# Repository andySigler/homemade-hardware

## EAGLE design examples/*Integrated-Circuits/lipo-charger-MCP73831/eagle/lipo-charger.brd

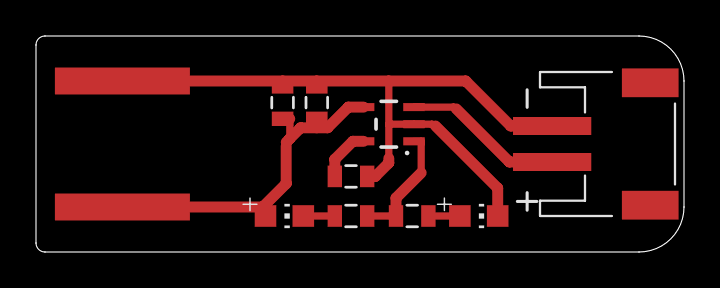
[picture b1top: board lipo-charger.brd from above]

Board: 2 copper layers, 36.0 x 12.0 mm, 10 parts (0 on the bottom side), 7 nets.

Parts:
C1: 10uF; 0805
C2: 0.1uF; 0805
IC1: IC_LIPO_CHARGER; SOT23-5
LED1: Red; CHIP-LED0805
LED2: Blue; CHIP-LED0805
R1, R2: 1k; 0805
R3: 10k; 0805
U$1: CONN_BATTERY-LIPO-HORIZ; JST-PH-2-SMT-RA
U$2: CONN_USB_PCB_POWER; USB-PCB-POWER

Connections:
5V: C1.1, C2.1, IC1.4, LED1.A, U$2.5V
BATTERY: IC1.3, U$1.1
CURRENT-CONTROL: IC1.5, R3.2
GND: C1.2, C2.2, IC1.2, LED2.C, R3.1, U$1.2, U$2.GND
unnamed: LED1.C, R1.2
unnamed: LED2.A, R2.1
STATUS: IC1.1, R1.1, R2.2

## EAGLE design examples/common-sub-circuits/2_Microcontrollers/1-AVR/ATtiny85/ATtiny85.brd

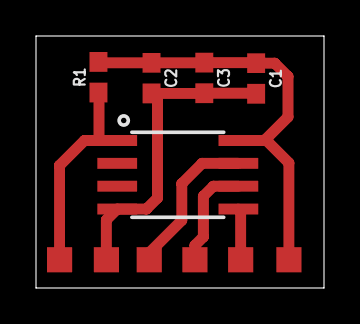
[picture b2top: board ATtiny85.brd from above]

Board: 2 copper layers, 16.0 x 14.0 mm, 11 parts (0 on the bottom side), 6 nets.

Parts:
C1: 0.1uF; 0603
C2, C3: 4.7uF; 0603
GND: TPSTP14SQ; TP14SQ
MISO: TPSTP14SQ; TP14SQ
MOSI: TPSTP14SQ; TP14SQ
R1: 10k; 0603
RESET: TPSTP14SQ; TP14SQ
SCK: TPSTP14SQ; TP14SQ
U1: Tiny85-20-SMT; SO08-EIAJ_MCU
VCC: TPSTP14SQ; TP14SQ

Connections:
GND: C1.2, C2.2, C3.2, GND.TP, U1.4
MISO: MISO.TP, U1.6
MOSI: MOSI.TP, U1.5
RESET: R1.1, RESET.TP, U1.1
SCK: SCK.TP, U1.7
VCC: C1.1, C2.1, C3.1, R1.2, U1.8, VCC.TP

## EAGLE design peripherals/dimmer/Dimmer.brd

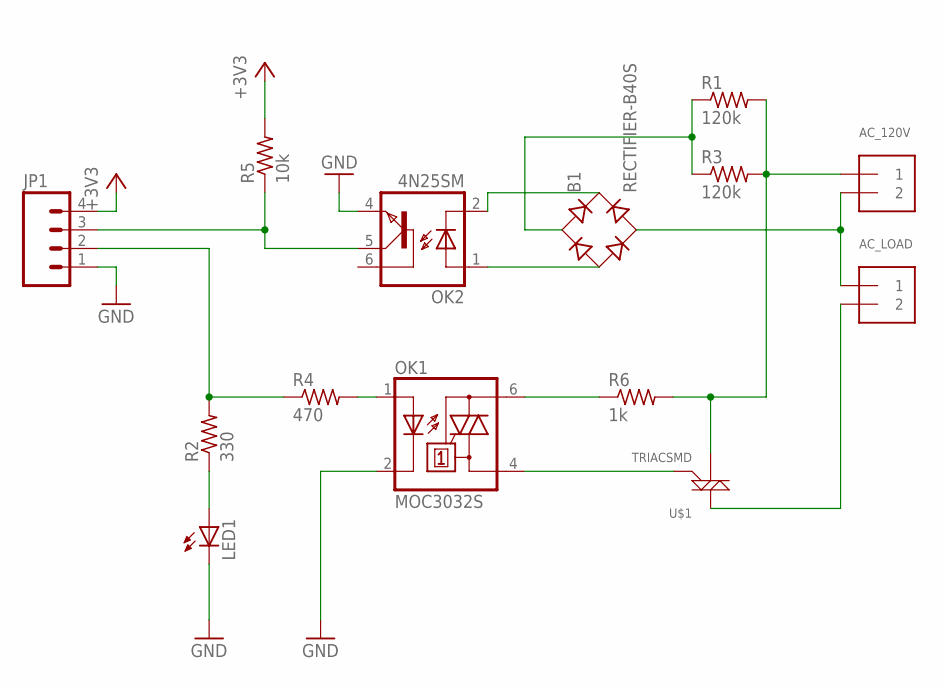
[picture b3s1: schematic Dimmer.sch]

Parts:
AC_120V: TERMBLOCK_1X2; TERMBLOCK_1X2-3.5MM
AC_LOAD: TERMBLOCK_1X2; TERMBLOCK_1X2-3.5MM
B1: RECTIFIER-B40S; B40S
JP1: M04LONGPADS; 1X04_LONGPADS
LED1: LEDCHIPLED_0603; CHIPLED_0603
OK1: MOC3032S; DIL6-SMD
OK2: 4N25SM; DIL6-SMD
R1, R3: 120k; R2512
R2: 330; R0603
R4: 470; R0603
R5: 10k; R0603
R6: 1k; R2512
U$1: TRIACSMD; SOT223

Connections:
+3V3: JP1.4, R5.2
GND: JP1.1, LED1.C, OK1.2 (C), OK2.4 (EMI)
unnamed: JP1.3, OK2.5 (COL), R5.1
unnamed: B1.AC1, R1.1, R3.1
unnamed: B1.-, OK2.1 (A)
unnamed: AC_120V.2, AC_LOAD.1, B1.AC2
unnamed: OK1.6 (A2), R6.1
unnamed: LED1.A, R2.1
unnamed: OK1.1 (A), R4.2
unnamed: JP1.2, R2.2, R4.1
unnamed: OK1.4 (A1), U$1.3 (G)
unnamed: AC_LOAD.2, U$1.2 (M2)
unnamed: AC_120V.1, R1.2, R3.2, R6.2, U$1.1 (M1)
unnamed: B1.+, OK2.2 (C)

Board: 2 copper layers, 14 parts (0 on the bottom side), 14 nets, no tracks yet.

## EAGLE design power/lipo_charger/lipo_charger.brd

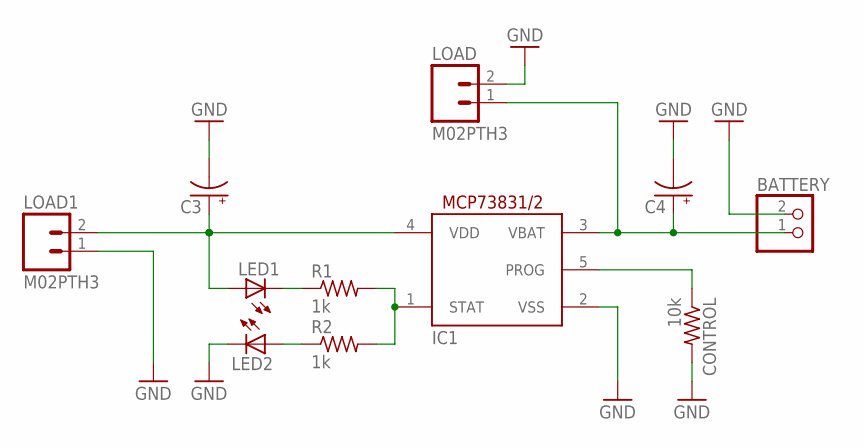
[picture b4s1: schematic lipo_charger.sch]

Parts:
BATTERY: JST_2PIN-SMT-RA; JST-PH-2-SMT-RA
C3, C4: CAP_POL1206; EIA3216
CONTROL: 10k; R0603
IC1: MCP73831/OT; SOT23-5L
LED1, LED2: LEDCHIPLED_0603; CHIPLED_0603
LOAD, LOAD1: M02PTH3; 1X02_LONGPADS
R1, R2: 1k; R0603

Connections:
GND: BATTERY.2 (1), C3.C (-), C4.C (-), CONTROL.2, IC1.2 (VSS), LED2.C, LOAD.2, LOAD1.1
unnamed: C3.A (+), IC1.4 (VDD), LED1.A, LOAD1.2
unnamed: LED1.C, R1.1
unnamed: LED2.A, R2.1
unnamed: IC1.1 (STAT), R1.2, R2.2
unnamed: BATTERY.1 (2), C4.A (+), IC1.3 (VBAT), LOAD.1
unnamed: CONTROL.1, IC1.5 (PROG)

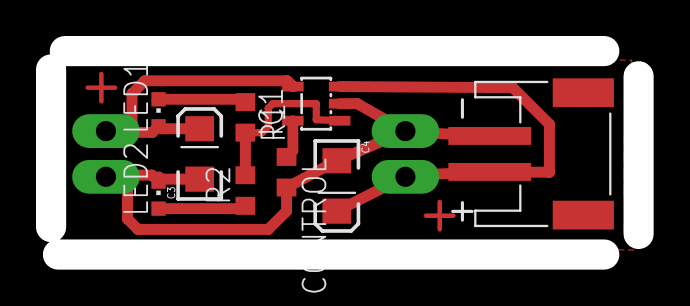
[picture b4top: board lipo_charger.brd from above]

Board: 2 copper layers, 32.6 x 11.3 mm, 11 parts (0 on the bottom side), 7 nets.

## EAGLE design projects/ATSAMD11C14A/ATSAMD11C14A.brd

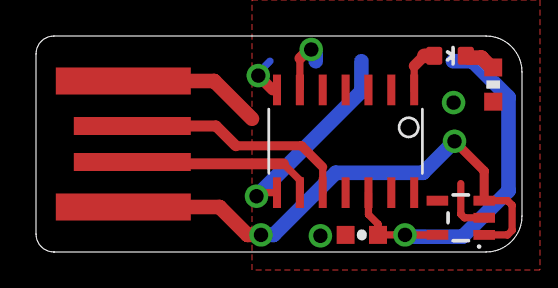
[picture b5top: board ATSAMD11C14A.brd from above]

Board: 2 copper layers, 27.0 x 12.0 mm, 7 parts (1 on the bottom side), 10 nets.

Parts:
C2: 0.1uF; 0603-CAP
LED1: blue; LED-0603
R2: 220; 0603-RES
U2: ATSAMD11C14-; SOIC14
U$1: HEADER-5-TESTPOINT; TESTPOINT-5
U$2: USB_CONN_UNSHIELDED; USB-A-PCB
U$3: REGULATOR3.3V-0.5A-MIC5219; SOT23-5

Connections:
5V: U$2.5V, U$3.1, U$3.3
GND: C2.2, R2.1, U2.11, U$1.4, U$2.GND, U$3.2
LED: LED1.A, U2.1
unnamed: LED1.C, R2.2
RESET: U2.6, U$1.2
SWDCLK: U2.7, U$1.1
SWDIO: U2.8, U$1.3
USB_D+: U2.10, U$2.USB_P
USB_D-: U2.9, U$2.USB_M
VCC: C2.1, U2.12, U$1.5, U$3.5

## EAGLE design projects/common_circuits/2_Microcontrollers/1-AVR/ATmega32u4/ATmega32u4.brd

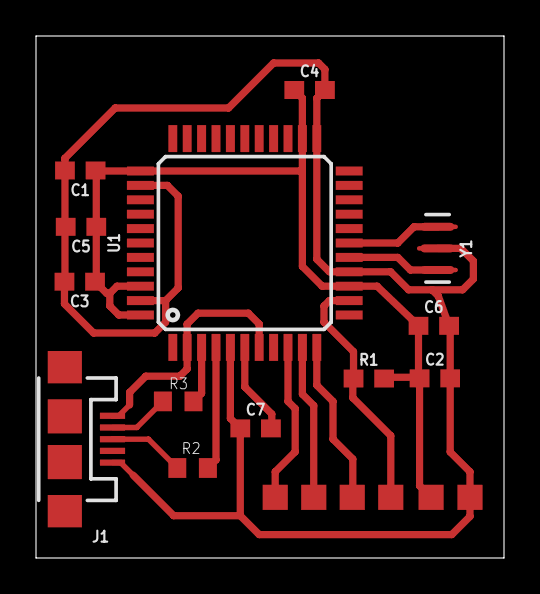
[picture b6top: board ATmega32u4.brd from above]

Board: 2 copper layers, 26.0 x 29.0 mm, 19 parts (0 on the bottom side), 14 nets.

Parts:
C1, C6, C7: 0.1uF; 0603
C2, C3, C4, C5: 4.7uF; 0603
GND: TPSTP14SQ; TP14SQ
J1: USB-MICROB
MISO: TPSTP14SQ; TP14SQ
MOSI: TPSTP14SQ; TP14SQ
R1: 10k; 0603
R2, R3: 22ohm; R0603
RESET: TPSTP14SQ; TP14SQ
SCK: TPSTP14SQ; TP14SQ
U1: 32U4; TQFP44
VCC: TPSTP14SQ; TP14SQ
Y1: 16MHz; RESONATOR-SMD-3.2X1.3

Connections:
D+: R2.1, U1.4
D-: R3.1, U1.3
GND: C1.2, C2.2, C3.2, C4.2, C5.2, C6.2, C7.1, GND.TP, J1.GND, U1.5, U1.15, U1.23, U1.35, U1.43, Y1.2
MISO: MISO.TP, U1.10
MOSI: MOSI.TP, U1.11
unnamed: C7.2, U1.6
unnamed: U1.17, Y1.1
unnamed: U1.16, Y1.3
unnamed: J1.D-, R3.2
unnamed: J1.D+, R2.2
RESET: R1.1, RESET.TP, U1.13
SCK: SCK.TP, U1.9
VBUS: J1.VBUS, U1.2, U1.7
VCC: C1.1, C2.1, C3.1, C4.1, C5.1, C6.1, R1.2, U1.14, U1.24, U1.34, U1.42, U1.44, VCC.TP

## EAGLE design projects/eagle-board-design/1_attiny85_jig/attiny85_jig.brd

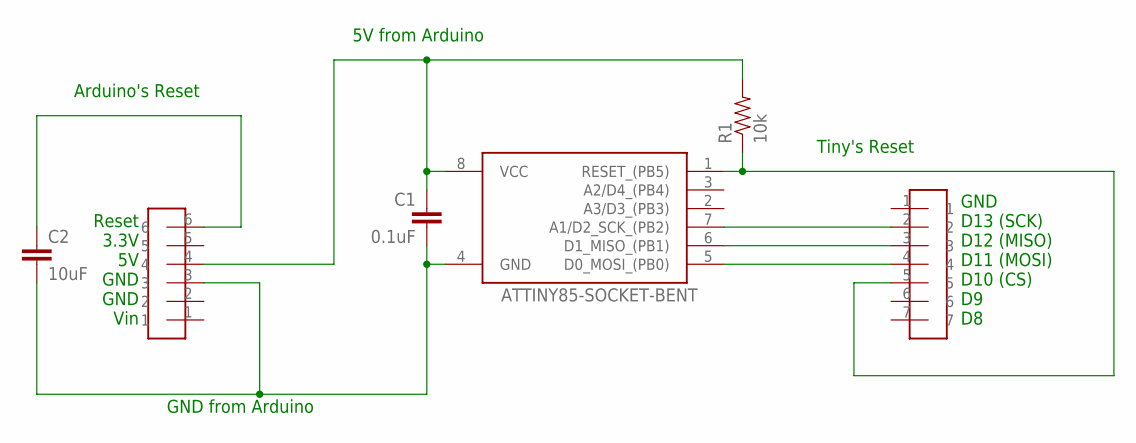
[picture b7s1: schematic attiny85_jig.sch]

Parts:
C1: 0.1uF; 0805
C2: 10uF; 0805
R1: 10k; 0805
U$1: ATTINY85-SOCKET-BENT; SOCKET-8PIN-BENT
U$2: HEADER-6
U$3: HEADER-7

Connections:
5V: C1.1, R1.2, U$1.8 (VCC), U$2.4
ARDUINO_RESET: C2.1, U$2.6
GND: C1.2, C2.2, U$1.4 (GND), U$2.3
MISO: U$1.6 (D1_MISO_(PB1)), U$3.3
MOSI: U$1.5 (D0_MOSI_(PB0)), U$3.4
SCK: U$1.7 (A1/D2_SCK_(PB2)), U$3.2
TINY_RESET: R1.1, U$1.1 (RESET_(PB5)), U$3.5

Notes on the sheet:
Arduino's Reset
GND D13 (SCK) D12 (MISO) D11 (MOSI) D10 (CS) D9 D8
Reset 3.3V 5V GND GND Vin
5V from Arduino
GND from Arduino
Tiny's Reset

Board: 2 copper layers, 6 parts (0 on the bottom side), 7 nets, no tracks yet.

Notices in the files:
parts and their libraries:
SparkFun-Resistors: Licensing: Creative Commons ShareAlike 4.0 International - https://creativecommons.org/licenses/by-sa/4.0
microbuilder: This work is placed in the public domain, and may be freely used for commercial and non-commercial work with the following conditions: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
